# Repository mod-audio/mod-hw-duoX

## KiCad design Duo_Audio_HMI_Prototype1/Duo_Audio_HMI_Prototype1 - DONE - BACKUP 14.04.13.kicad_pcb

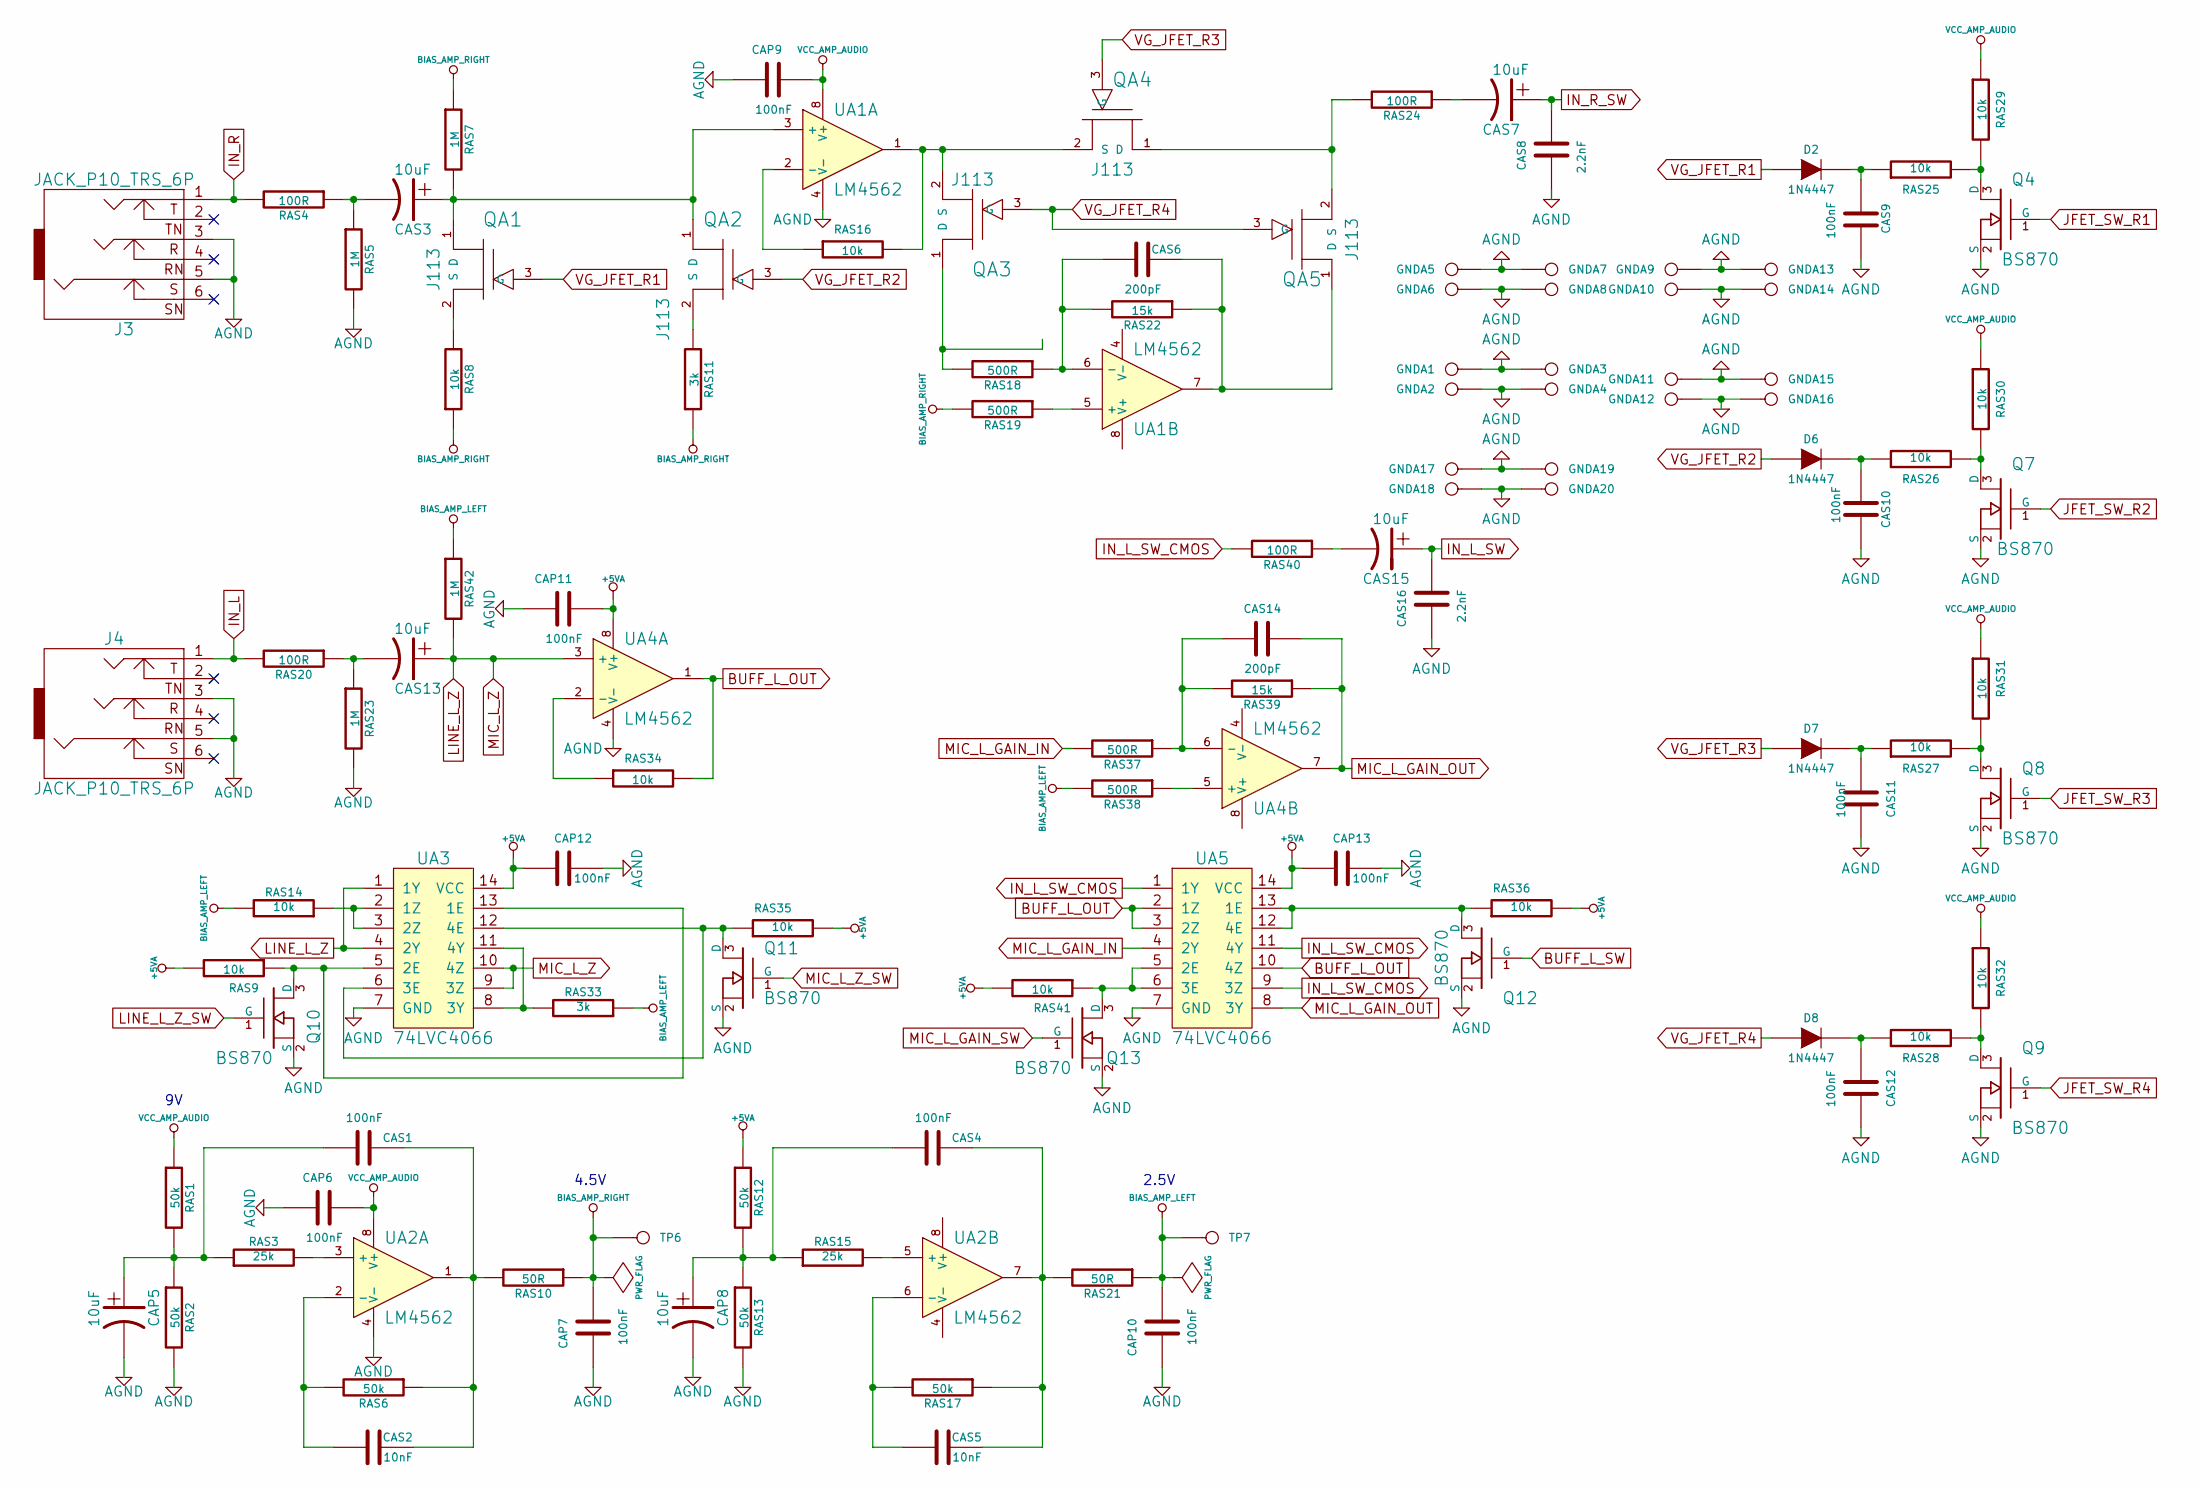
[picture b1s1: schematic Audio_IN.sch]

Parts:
CAP5, CAP8: 10uF; CAP_RAD_5MM
CAP6, CAP7, CAP9, CAP10, CAP11, CAP12, CAP13: 100nF; SM0603
CAS1, CAS4, CAS9, CAS10, CAS11, CAS12: 100nF; SM0603
CAS2, CAS5: 10nF; SM0603
CAS3, CAS7, CAS13, CAS15: 10uF; CAP_RAD_5MM
CAS6, CAS14: 200pF; SM0603
CAS8, CAS16: 2.2nF; SM0603
D2, D6, D7, D8: 1N4447; DO-35
GNDA1, GNDA2, GNDA3, GNDA4, GNDA5, GNDA6, GNDA7, GNDA8, GNDA9, GNDA10, GNDA11, GNDA12, GNDA13, GNDA14, GNDA15, GNDA16, GNDA17, GNDA18, GNDA19, GNDA20: CONN_1; PAD_GND
J3, J4: JACK_P10_TRS_6P; JACK-NMJ6HCD2_1
Q4, Q7, Q8, Q9, Q10, Q11, Q12, Q13: BS870; SOT23
QA1, QA2, QA3, QA4, QA5: J113; TO92_
RAS1, RAS2, RAS6, RAS12, RAS13, RAS17: 50k; RES_PTH_6MM
RAS3, RAS15: 25k; RES_PTH_6MM
RAS4, RAS20, RAS24, RAS40: 100R; RES_PTH_6MM
RAS5, RAS7, RAS23, RAS42: 1M; RES_PTH_6MM
RAS8, RAS14, RAS16, RAS25, RAS26, RAS27, RAS28, RAS29, RAS30, RAS31, RAS32, RAS34: 10k; RES_PTH_6MM
RAS9, RAS35, RAS36, RAS41: 10k; SM0603
RAS10, RAS21: 50R; RES_PTH_6MM
RAS11, RAS33: 3k; RES_PTH_6MM
RAS18, RAS19, RAS37, RAS38: 500R; RES_PTH_6MM
RAS22, RAS39: 15k; RES_PTH_6MM
TP6, TP7: CONN_1; SIL-1
UA1, UA2, UA4: LM4562; SO8E
UA3, UA5: 74LVC4066; SO14E

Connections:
+5VA: CAP11.2, CAP12.2, CAP13.2, RAS9.2, RAS12.1, RAS35.2, RAS36.2, RAS41.2, UA3.14 (VCC), UA4.8 (V+), UA5.14 (VCC); also elsewhere on the board
AGND: CAP5.2, CAP6.1, CAP7.1, CAP8.2, CAP9.1, CAP10.1, CAP11.1, CAP12.1, CAP13.1, CAS8.1, CAS9.2, CAS10.2, CAS11.2, CAS12.2, CAS16.1, GNDA1.1, GNDA2.1, GNDA3.1, GNDA4.1, GNDA5.1, GNDA6.1, GNDA7.1, GNDA8.1, GNDA9.1, GNDA10.1, GNDA11.1, GNDA12.1, GNDA13.1, GNDA14.1, GNDA15.1, GNDA16.1, GNDA17.1, GNDA18.1, GNDA19.1, GNDA20.1, J3.3, J3.5, J4.3, J4.5, Q4.2 (S), Q7.2 (S), Q8.2 (S), Q9.2 (S), Q10.2 (S), Q11.2 (S), Q12.2 (S), Q13.2 (S), RAS2.2, RAS5.2, RAS13.2, RAS23.2, UA1.4 (V-), UA2.4 (V-), UA3.7 (GND), UA4.4 (V-), UA5.7 (GND); also elsewhere on the board
BIAS_AMP_LEFT: CAP10.2, RAS14.2, RAS21.1, RAS33.1, RAS38.2, RAS42.1, TP7.1
BIAS_AMP_RIGHT: CAP7.2, RAS7.1, RAS8.1, RAS10.1, RAS11.1, RAS19.2, TP6.1
BUFF_L_OUT: RAS34.2, UA4.1, UA5.2 (1Z), UA5.3 (2Z), UA5.10 (4Z)
BUFF_L_SW: Q12.1 (G); also elsewhere on the board
IN_L: J4.1, RAS20.2; also elsewhere on the board
IN_L_SW: CAS15.1, CAS16.2; also elsewhere on the board
IN_L_SW_CMOS: RAS40.2, UA5.1 (1Y), UA5.9 (3Z), UA5.11 (4Y)
IN_R: J3.1, RAS4.2; also elsewhere on the board
IN_R_SW: CAS7.1, CAS8.2; also elsewhere on the board
JFET_SW_R1: Q4.1 (G); also elsewhere on the board
JFET_SW_R2: Q7.1 (G); also elsewhere on the board
JFET_SW_R3: Q8.1 (G); also elsewhere on the board
JFET_SW_R4: Q9.1 (G); also elsewhere on the board
LINE_L_Z: CAS13.1, RAS42.2, UA3.1 (1Y), UA3.4 (2Y), UA3.9 (3Z), UA3.10 (4Z), UA4.3 (+)
LINE_L_Z_SW: Q10.1 (G); also elsewhere on the board
MIC_L_GAIN_IN: RAS37.2, UA5.4 (2Y)
MIC_L_GAIN_OUT: CAS14.2, RAS39.1, UA4.7, UA5.8 (3Y)
MIC_L_GAIN_SW: Q13.1 (G); also elsewhere on the board
MIC_L_Z_SW: Q11.1 (G); also elsewhere on the board
unnamed: QA4.1 (D), QA5.2 (S), RAS24.2
unnamed: QA2.2 (S), RAS11.2
unnamed: QA1.2 (S), RAS8.2
unnamed: CAS13.2, RAS20.1, RAS23.1
unnamed: QA3.1 (D), RAS18.2
unnamed: Q9.3 (D), RAS28.2, RAS32.2
unnamed: CAS15.2, RAS40.1
unnamed: RAS14.1, UA3.2 (1Z), UA3.3 (2Z)
unnamed: RAS34.1, UA4.2 (-)
unnamed: RAS38.1, UA4.5 (+)
unnamed: CAS14.1, RAS37.1, RAS39.2, UA4.6 (-)
unnamed: CAS5.1, RAS17.2, UA2.6 (-)
unnamed: CAS3.2, RAS4.1, RAS5.1
unnamed: CAS3.1, QA1.1 (D), QA2.1 (D), RAS7.2, UA1.3 (+)
unnamed: RAS16.1, UA1.2 (-)
unnamed: CAP8.1, CAS4.1, RAS12.2, RAS13.1, RAS15.1
unnamed: RAS15.2, UA2.5 (+)
unnamed: CAS4.2, CAS5.2, RAS17.1, RAS21.2, UA2.7
unnamed: CAS7.2, RAS24.1
unnamed: Q4.3 (D), RAS25.2, RAS29.2
unnamed: Q8.3 (D), RAS27.2, RAS31.2
unnamed: CAS6.2, QA5.1 (D), RAS22.1, UA1.7
unnamed: QA3.2 (S), QA4.2 (S), RAS16.2, UA1.1
unnamed: RAS19.1, UA1.5 (+)
unnamed: CAS6.1, RAS18.1, RAS22.2, UA1.6 (-)
unnamed: Q7.3 (D), RAS26.2, RAS30.2
unnamed: CAS12.1, D8.2 (K), RAS28.1
unnamed: CAS11.1, D7.2 (K), RAS27.1
unnamed: CAS10.1, D6.2 (K), RAS26.1
unnamed: CAS9.1, D2.2 (K), RAS25.1
unnamed: Q13.3 (D), RAS41.1, UA5.5 (2E), UA5.6 (3E)
unnamed: RAS33.2, UA3.8 (3Y), UA3.11 (4Y)
unnamed: Q11.3 (D), RAS35.1, UA3.6 (3E), UA3.12 (4E)
unnamed: Q10.3 (D), RAS9.1, UA3.5 (2E), UA3.13 (1E)
unnamed: Q12.3 (D), RAS36.1, UA5.12 (4E), UA5.13 (1E)
unnamed: CAP5.1, CAS1.1, RAS1.2, RAS2.1, RAS3.1
unnamed: CAS2.1, RAS6.2, UA2.2 (-)
unnamed: RAS3.2, UA2.3 (+)
unnamed: CAS1.2, CAS2.2, RAS6.1, RAS10.2, UA2.1
VCC_AMP_AUDIO: CAP6.2, CAP9.2, RAS1.1, RAS29.1, RAS30.1, RAS31.1, RAS32.1, UA1.8 (V+), UA2.8 (V+); also elsewhere on the board
VG_JFET_R1: D2.1 (A), QA1.3 (G)
VG_JFET_R2: D6.1 (A), QA2.3 (G)
VG_JFET_R3: D7.1 (A), QA4.3 (G)
VG_JFET_R4: D8.1 (A), QA3.3 (G), QA5.3 (G)

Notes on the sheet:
4.5V
2.5V

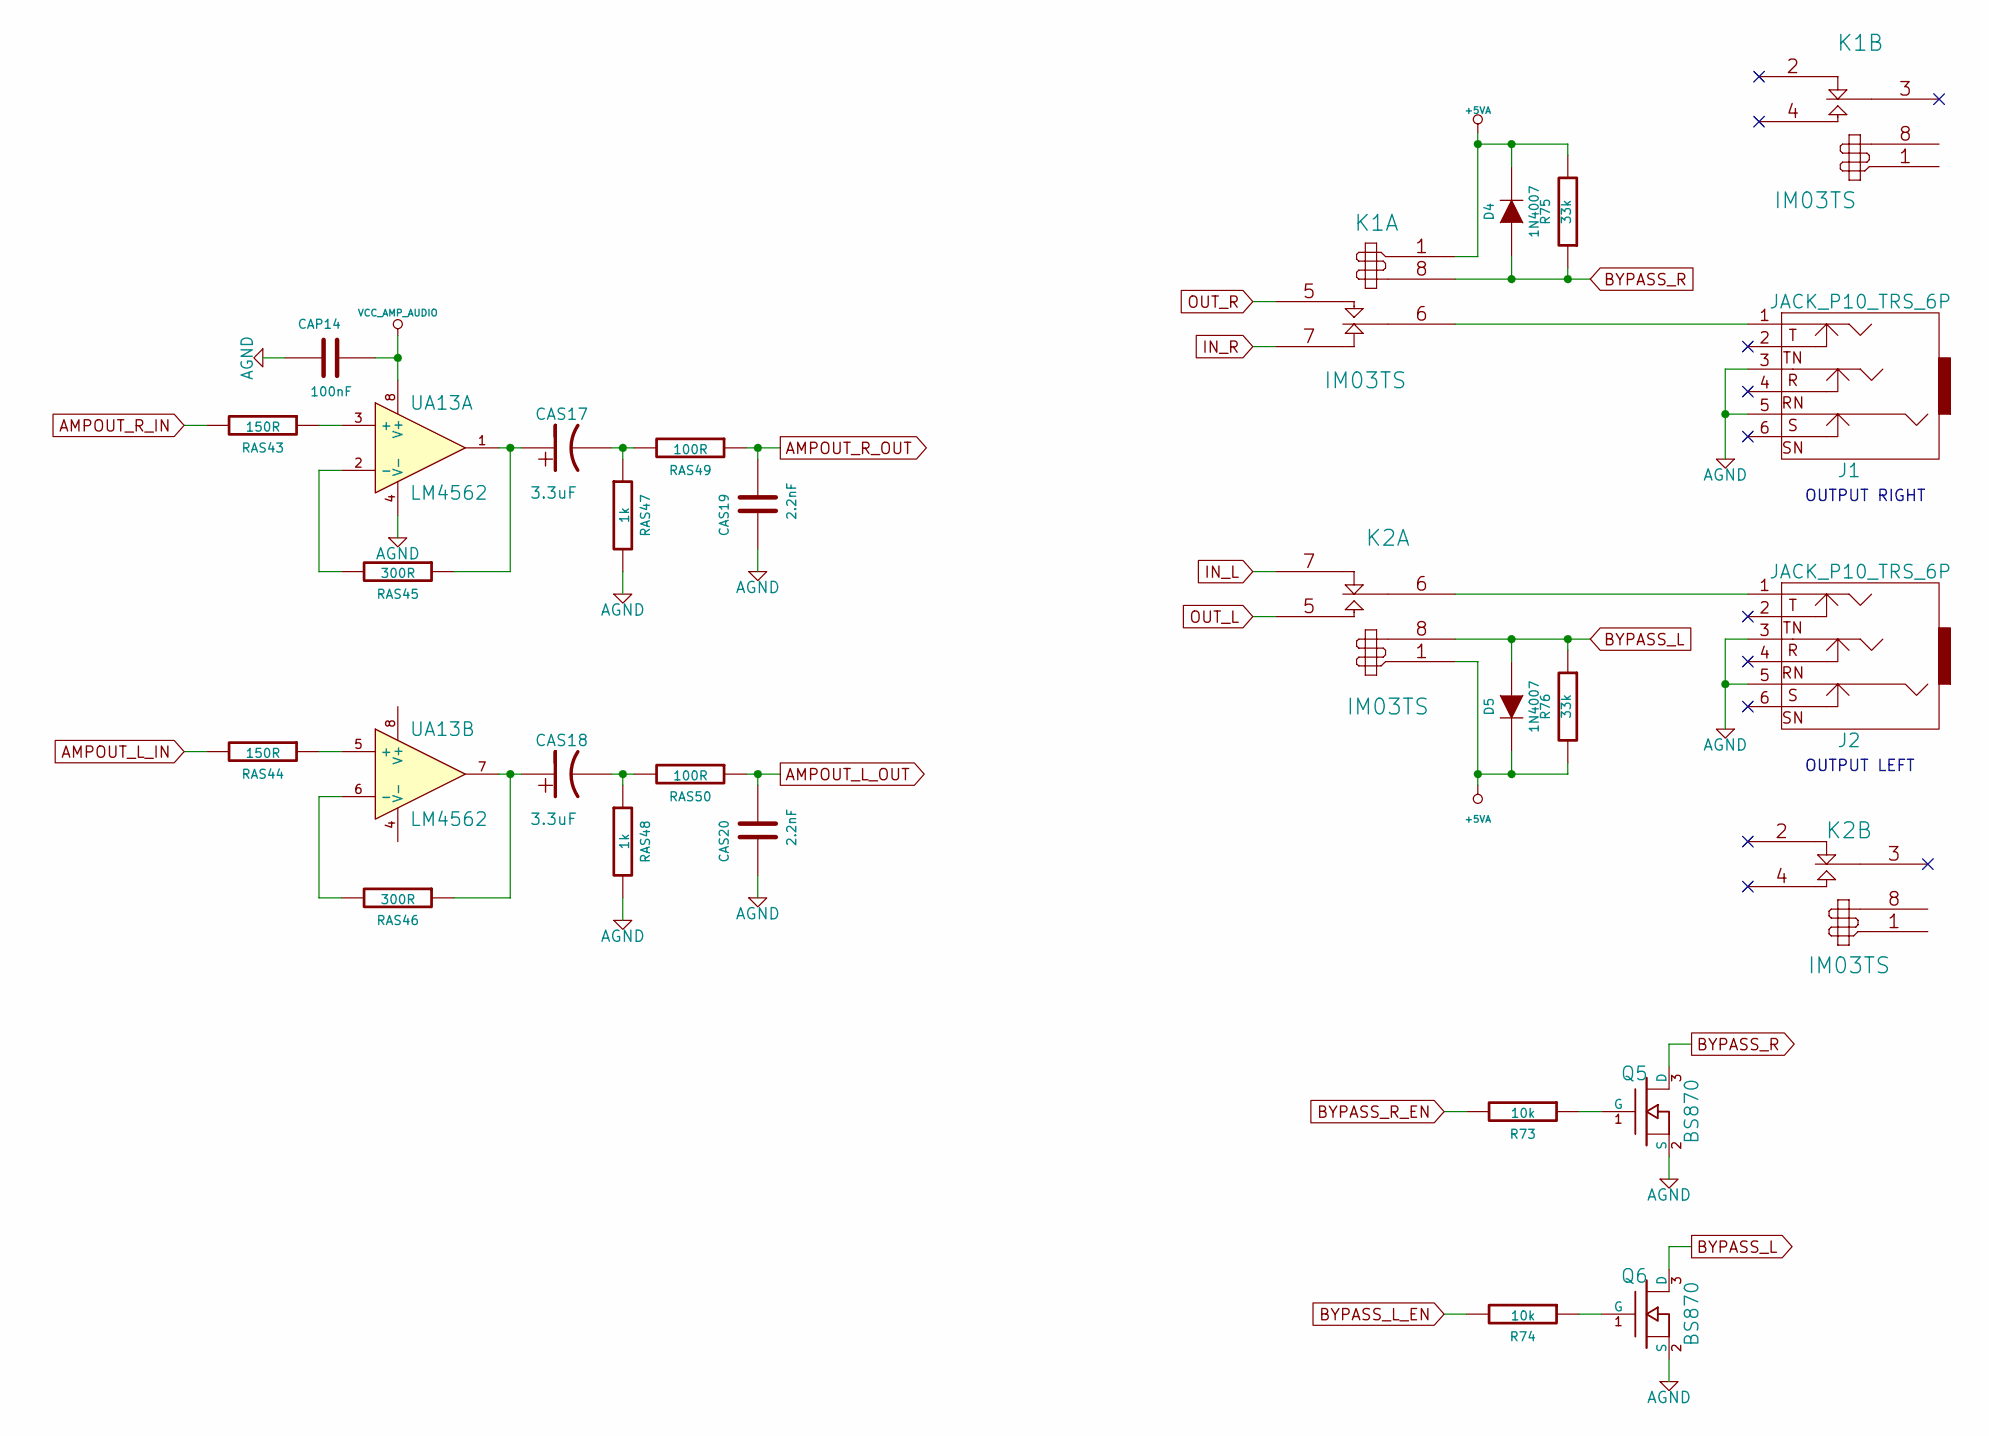
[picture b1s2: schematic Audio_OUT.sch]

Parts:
CAP14: 100nF; SM0603
CAS17, CAS18: 3.3uF; CAP_RAD_5MM
CAS19, CAS20: 2.2nF; SM0603
D4, D5: 1N4007; DO-214AC(SMA)
J1, J2: JACK_P10_TRS_6P; JACK-NMJ6HCD2_1
K1, K2: IM03TS
Q5, Q6: BS870; SOT23
R73, R74: 10k; SM0603
R75, R76: 33k; SM0603
RAS43, RAS44: 150R; RES_PTH_6MM
RAS45, RAS46: 300R; RES_PTH_6MM
RAS47, RAS48: 1k; RES_PTH_6MM
RAS49, RAS50: 100R; RES_PTH_6MM
UA13: LM4562; SO8E

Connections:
+5VA: D4.2 (K), D5.2 (K), K1.1, K2.1, R75.2, R76.2; also elsewhere on the board
AGND: CAP14.1, CAS19.1, CAS20.1, J1.3, J1.5, J2.3, J2.5, Q5.2 (S), Q6.2 (S), RAS47.2, RAS48.2, UA13.4 (V-); also elsewhere on the board
AMPOUT_L_IN: RAS44.2; also elsewhere on the board
AMPOUT_L_OUT: CAS20.2, RAS50.1; also elsewhere on the board
AMPOUT_R_IN: RAS43.2; also elsewhere on the board
AMPOUT_R_OUT: CAS19.2, RAS49.1; also elsewhere on the board
BYPASS_L: D5.1 (A), K2.8, Q6.3 (D), R76.1
BYPASS_L_EN: R74.2; also elsewhere on the board
BYPASS_R: D4.1 (A), K1.8, Q5.3 (D), R75.1
BYPASS_R_EN: R73.2; also elsewhere on the board
IN_L: K2.7 (R); also elsewhere on the board
IN_R: K1.7 (R); also elsewhere on the board
unnamed: RAS44.1, UA13.5 (+)
unnamed: CAS18.1, RAS46.1, UA13.7
unnamed: RAS46.2, UA13.6 (-)
unnamed: RAS43.1, UA13.3 (+)
unnamed: CAS17.2, RAS47.1, RAS49.2
unnamed: J1.1, K1.6 (C)
unnamed: J2.1, K2.6 (C)
unnamed: CAS18.2, RAS48.1, RAS50.2
unnamed: Q5.1 (G), R73.1
unnamed: Q6.1 (G), R74.1
unnamed: RAS45.2, UA13.2 (-)
unnamed: CAS17.1, RAS45.1, UA13.1
OUT_L: K2.5 (T); also elsewhere on the board
OUT_R: K1.5 (T); also elsewhere on the board
VCC_AMP_AUDIO: CAP14.2, UA13.8 (V+); also elsewhere on the board

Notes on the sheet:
OUTPUT RIGHT
OUTPUT LEFT

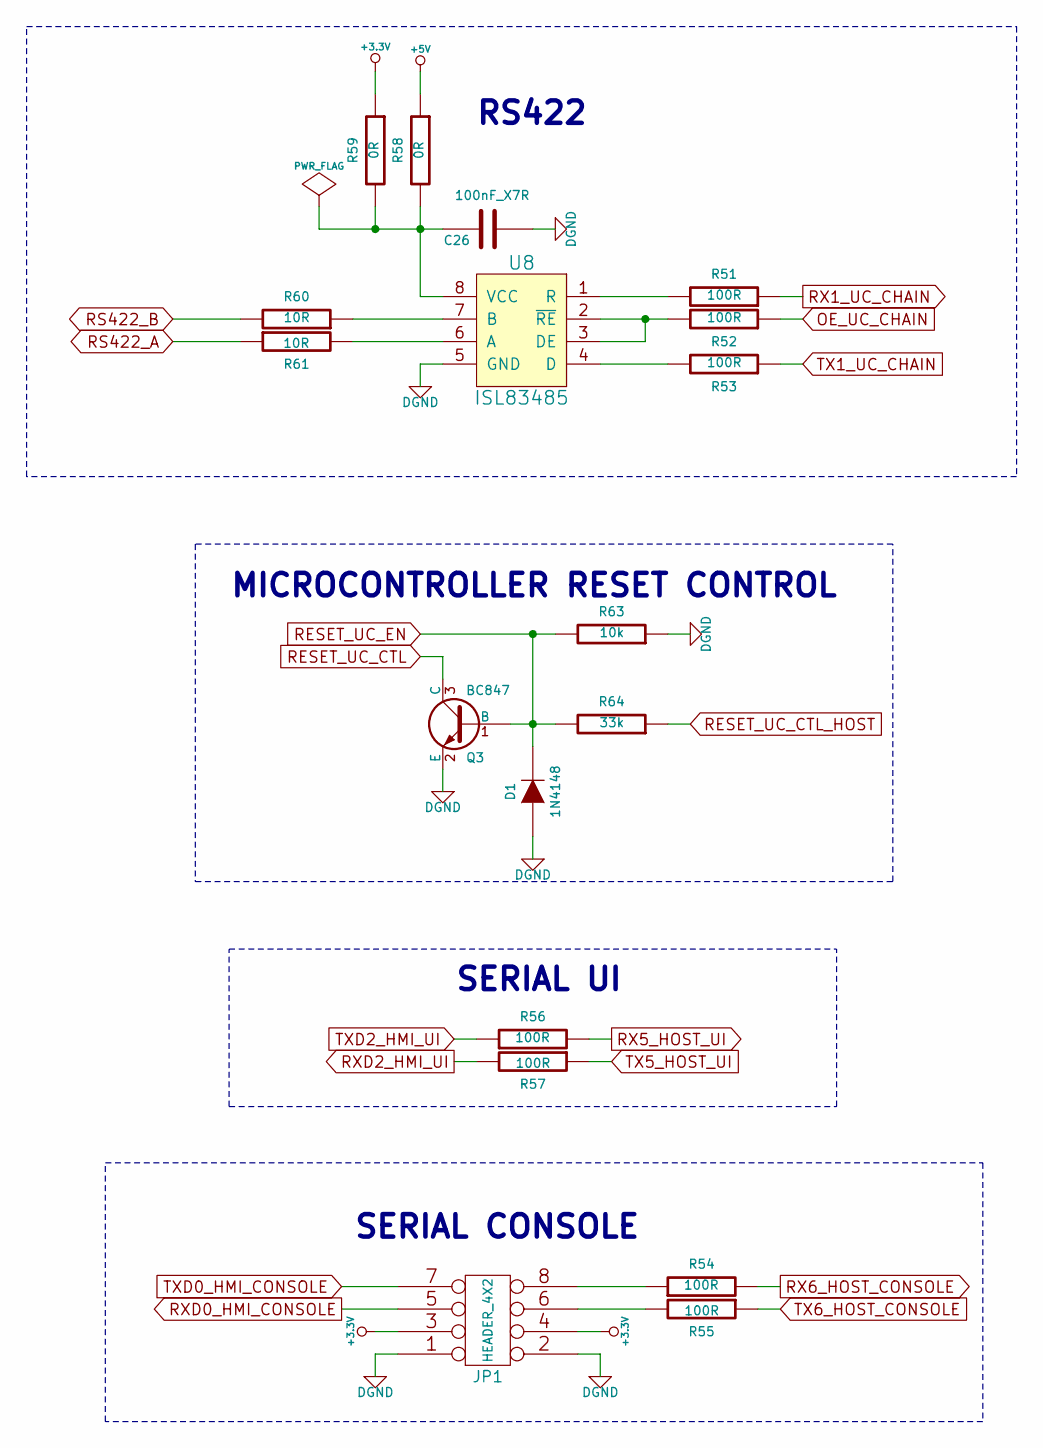
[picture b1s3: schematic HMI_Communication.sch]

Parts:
C26: 100nF_X7R; SM0603
D1: 1N4148; SOD323
JP1: HEADER_4X2; PIN_ARRAY_4X2
Q3: BC847; SOT23
R51, R52, R53, R54, R55, R56, R57: 100R; SM0603
R58, R59: 0R; SM0805
R60, R61: 10R; SM0805
R63: 10k; SM0603
R64: 33k; SM0603
U8: ISL83485; SO8E

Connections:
+3.3V: JP1.3, JP1.4, R59.1; also elsewhere on the board
+5V: R58.1; also elsewhere on the board
AGND: C26.1, D1.1 (A), JP1.1, JP1.2, Q3.2 (E), R63.1, U8.5 (GND); also elsewhere on the board
unnamed: R53.2, U8.4 (D)
unnamed: JP1.8, R54.1
unnamed: C26.2, R58.2, R59.2, U8.8 (VCC)
unnamed: R51.2, U8.1 (R)
unnamed: R61.2, U8.6 (A)
unnamed: R60.1, U8.7 (B)
unnamed: R52.2, U8.2 (~RE), U8.3 (DE)
unnamed: JP1.6, R55.2
OE_UC_CHAIN: R52.1; also elsewhere on the board
RESET_UC_CTL: Q3.3 (C); also elsewhere on the board
RESET_UC_CTL_HOST: R64.1; also elsewhere on the board
RESET_UC_EN: D1.2 (K), Q3.1 (B), R63.2, R64.2; also elsewhere on the board
RS422_A: R61.1; also elsewhere on the board
RS422_B: R60.2; also elsewhere on the board
RX1_UC_CHAIN: R51.1; also elsewhere on the board
RX5_HOST_UI: R56.2; also elsewhere on the board
RX6_HOST_CONSOLE: R54.2; also elsewhere on the board
RXD0_HMI_CONSOLE: JP1.5; also elsewhere on the board
RXD2_HMI_UI: R57.2; also elsewhere on the board
TX1_UC_CHAIN: R53.1; also elsewhere on the board
TX5_HOST_UI: R57.1; also elsewhere on the board
TX6_HOST_CONSOLE: R55.1; also elsewhere on the board
TXD0_HMI_CONSOLE: JP1.7; also elsewhere on the board
TXD2_HMI_UI: R56.1; also elsewhere on the board

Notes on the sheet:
RS422
SERIAL UI
SERIAL CONSOLE
MICROCONTROLLER RESET CONTROL

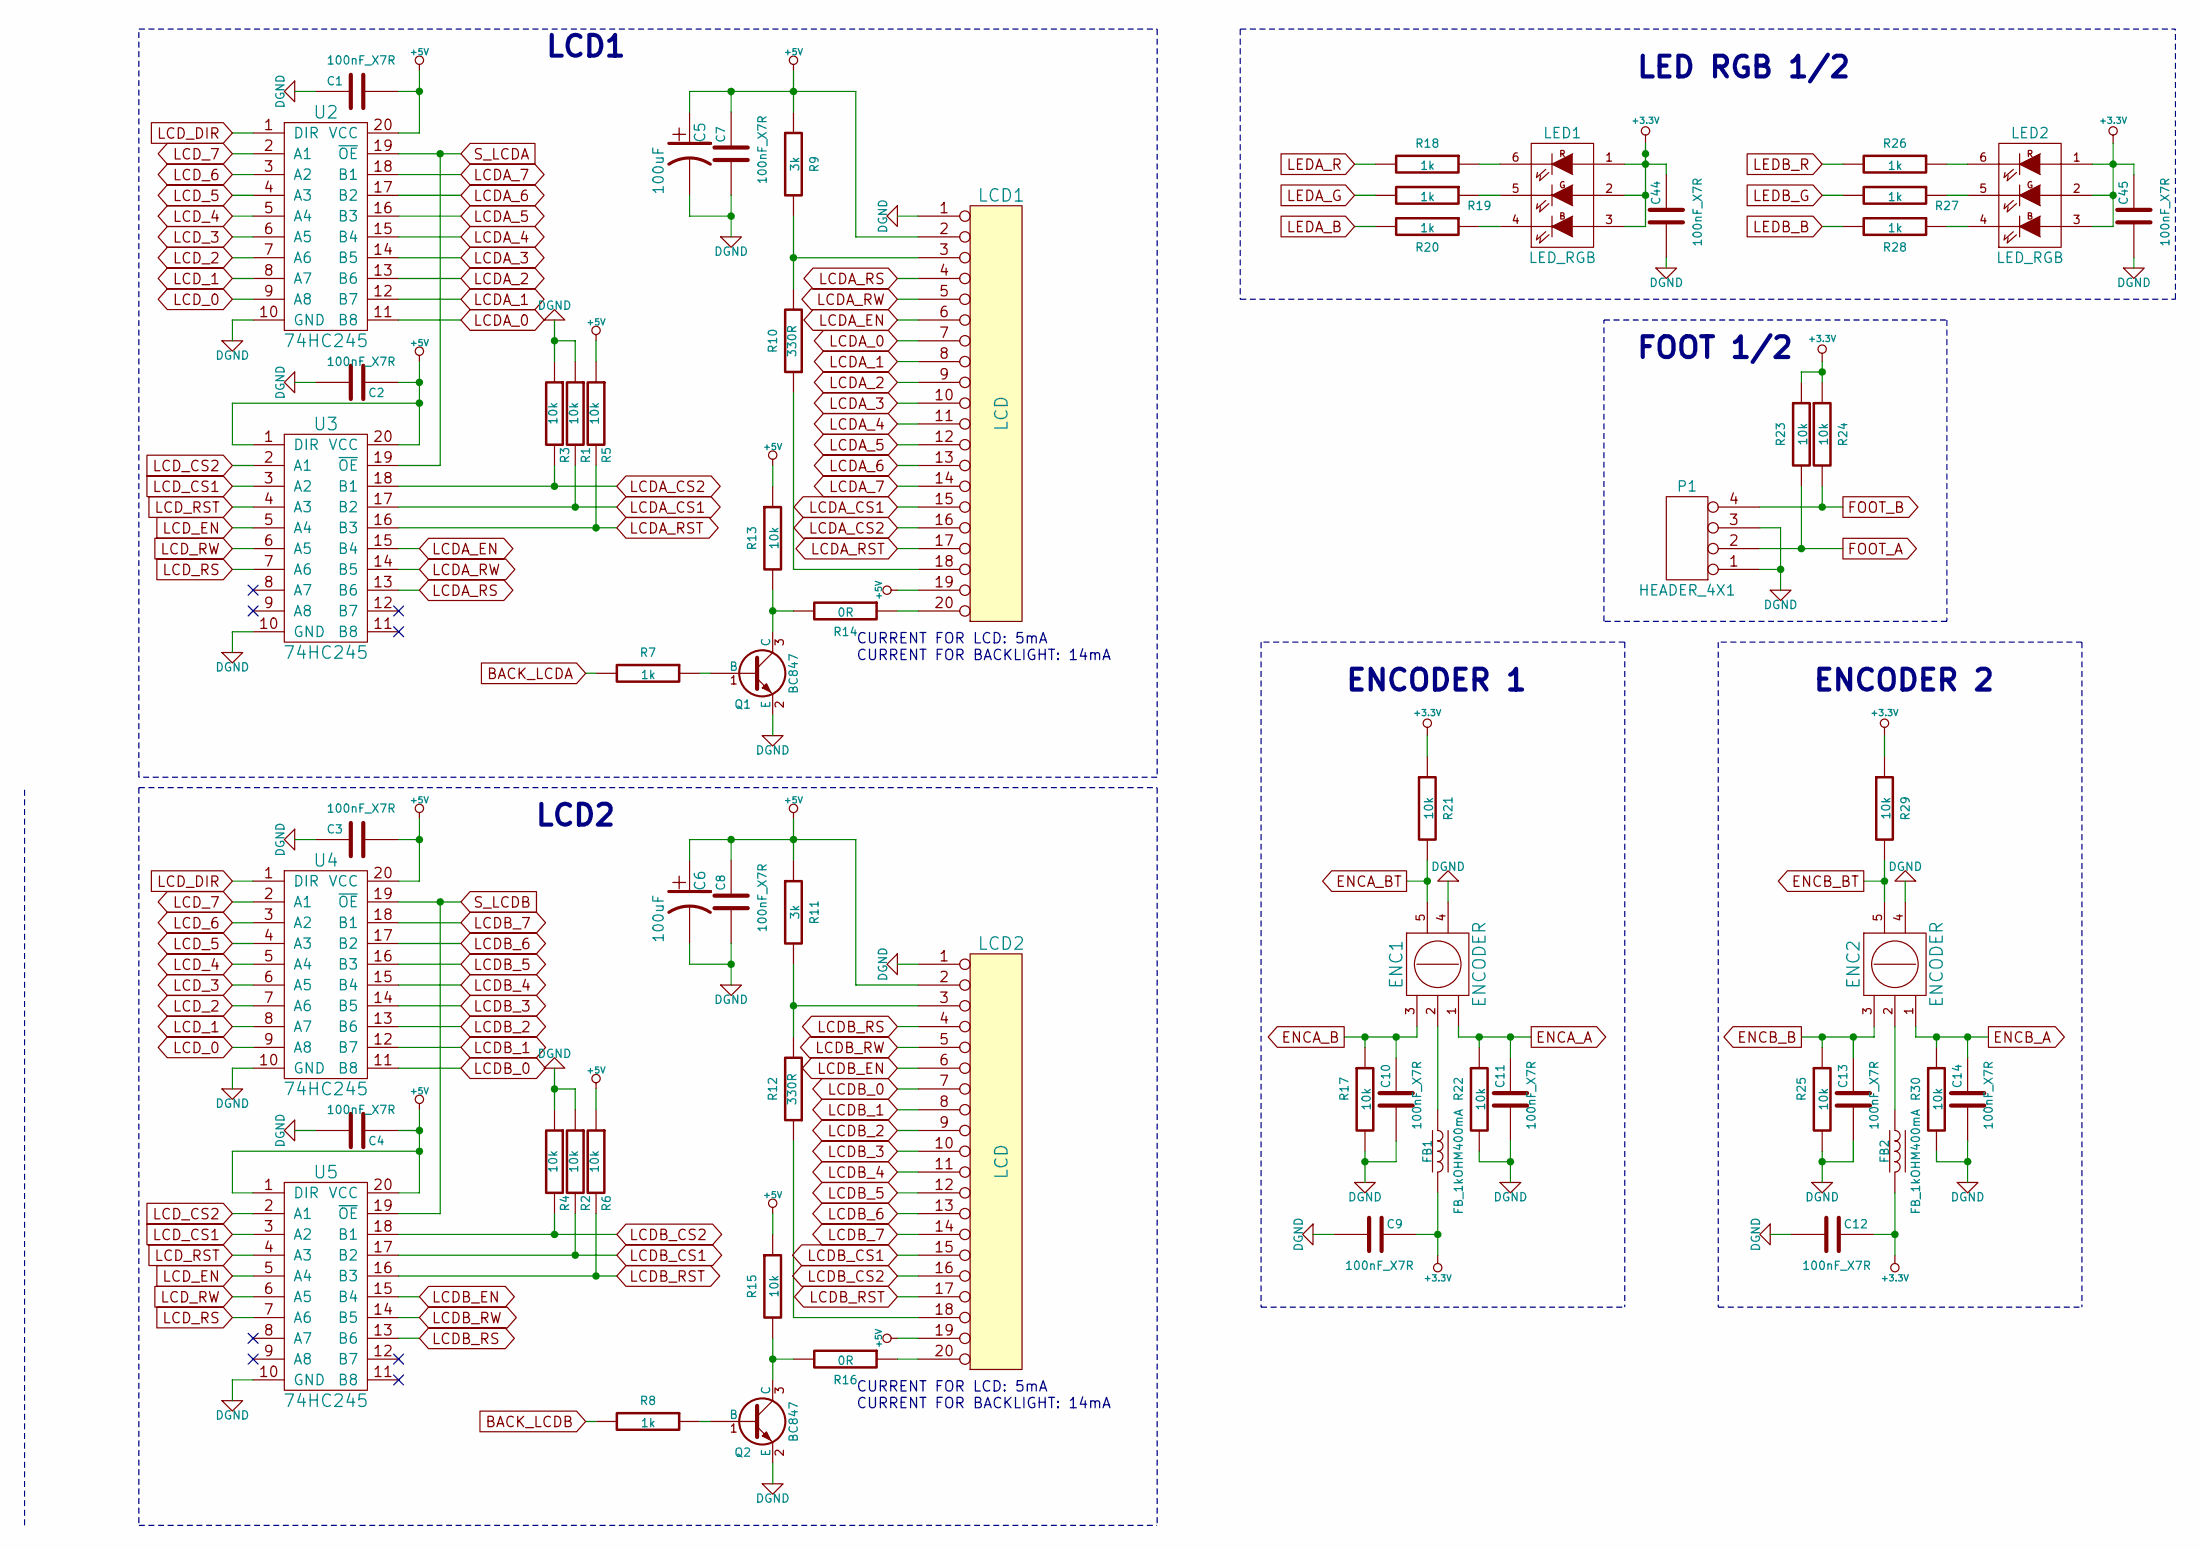
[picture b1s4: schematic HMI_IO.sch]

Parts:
C1, C2, C3, C4, C7, C8, C9, C10, C11, C12, C13, C14, C44, C45: 100nF_X7R; SM0603
C5, C6: 100uF; CAP_RAD_5MM
ENC1, ENC2: ENCODER; ENCODER_PEC11_4KS1
FB1, FB2: FB_1kOHM400mA; SM0805
LCD1, LCD2: LCD; LCD-AGM-12864E1-201_1
LED1, LED2: LED_RGB; LED_CLRTB_GFSF_1
P1: HEADER_4X1; PIN_ARRAY_4x1
Q1, Q2: BC847; SOT23
R1, R2, R3, R4, R5, R6, R13, R15, R17, R21, R22, R23, R24, R25, R29, R30: 10k; SM0603
R7, R8, R18, R19, R20, R26, R27, R28: 1k; SM0603
R9, R11: 3k; SM0603
R10, R12: 330R; SM0603
R14, R16: 0R; SM0805
U2, U3, U4, U5: 74HC245; TSSOP20

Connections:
+3.3V: C9.1, C12.1, C44.1, C45.1, FB1.1, FB2.1, LED1.1 (AR), LED1.2 (AG), LED1.3 (AB), LED2.1 (AR), LED2.2 (AG), LED2.3 (AB), R21.1, R23.1, R24.1, R29.1; also elsewhere on the board
+5V: C1.1, C2.1, C3.1, C4.1, C5.1, C6.1, C7.1, C8.1, LCD1.2, LCD1.19, LCD2.2, LCD2.19, R5.1, R6.1, R9.1, R11.1, R13.1, R15.1, U2.20 (VCC), U3.1 (DIR), U3.20 (VCC), U4.20 (VCC), U5.1 (DIR), U5.20 (VCC); also elsewhere on the board
AGND: C1.2, C2.2, C3.2, C4.2, C5.2, C6.2, C7.2, C8.2, C9.2, C10.2, C11.2, C12.2, C13.2, C14.2, C44.2, C45.2, ENC1.4, ENC2.4, LCD1.1, LCD2.1, P1.1, P1.3, Q1.2 (E), Q2.2 (E), R1.1, R2.1, R3.1, R4.1, R17.2, R22.2, R25.2, R30.2, U2.10 (GND), U3.10 (GND), U4.10 (GND), U5.10 (GND); also elsewhere on the board
BACK_LCDA: R7.2; also elsewhere on the board
BACK_LCDB: R8.2; also elsewhere on the board
ENCA_A: C11.1, ENC1.1, R22.1; also elsewhere on the board
ENCA_B: C10.1, ENC1.3, R17.1; also elsewhere on the board
ENCA_BT: ENC1.5, R21.2; also elsewhere on the board
ENCB_A: C14.1, ENC2.1, R30.1; also elsewhere on the board
ENCB_B: C13.1, ENC2.3, R25.1; also elsewhere on the board
ENCB_BT: ENC2.5, R29.2; also elsewhere on the board
FOOT_A: P1.2, R23.2; also elsewhere on the board
FOOT_B: P1.4, R24.2; also elsewhere on the board
LCDA_0: LCD1.7, U2.11 (B8)
LCDA_1: LCD1.8, U2.12 (B7)
LCDA_2: LCD1.9, U2.13 (B6)
LCDA_3: LCD1.10, U2.14 (B5)
LCDA_4: LCD1.11, U2.15 (B4)
LCDA_5: LCD1.12, U2.16 (B3)
LCDA_6: LCD1.13, U2.17 (B2)
LCDA_7: LCD1.14, U2.18 (B1)
LCDA_CS1: LCD1.15, R1.2, U3.17 (B2)
LCDA_CS2: LCD1.16, R3.2, U3.18 (B1)
LCDA_EN: LCD1.6, U3.15 (B4)
LCDA_RS: LCD1.4, U3.13 (B6)
LCDA_RST: LCD1.17, R5.2, U3.16 (B3)
LCDA_RW: LCD1.5, U3.14 (B5)
LCDB_0: LCD2.7, U4.11 (B8)
LCDB_1: LCD2.8, U4.12 (B7)
LCDB_2: LCD2.9, U4.13 (B6)
LCDB_3: LCD2.10, U4.14 (B5)
LCDB_4: LCD2.11, U4.15 (B4)
LCDB_5: LCD2.12, U4.16 (B3)
LCDB_6: LCD2.13, U4.17 (B2)
LCDB_7: LCD2.14, U4.18 (B1)
LCDB_CS1: LCD2.15, R2.2, U5.17 (B2)
LCDB_CS2: LCD2.16, R4.2, U5.18 (B1)
LCDB_EN: LCD2.6, U5.15 (B4)
LCDB_RS: LCD2.4, U5.13 (B6)
LCDB_RST: LCD2.17, R6.2, U5.16 (B3)
LCDB_RW: LCD2.5, U5.14 (B5)
LCD_0: U2.9 (A8), U4.9 (A8); also elsewhere on the board
LCD_1: U2.8 (A7), U4.8 (A7); also elsewhere on the board
LCD_2: U2.7 (A6), U4.7 (A6); also elsewhere on the board
LCD_3: U2.6 (A5), U4.6 (A5); also elsewhere on the board
LCD_4: U2.5 (A4), U4.5 (A4); also elsewhere on the board
LCD_5: U2.4 (A3), U4.4 (A3); also elsewhere on the board
LCD_6: U2.3 (A2), U4.3 (A2); also elsewhere on the board
LCD_7: U2.2 (A1), U4.2 (A1); also elsewhere on the board
LCD_CS1: U3.3 (A2), U5.3 (A2); also elsewhere on the board
LCD_CS2: U3.2 (A1), U5.2 (A1); also elsewhere on the board
LCD_DIR: U2.1 (DIR), U4.1 (DIR); also elsewhere on the board
LCD_EN: U3.5 (A4), U5.5 (A4); also elsewhere on the board
LCD_RS: U3.7 (A6), U5.7 (A6); also elsewhere on the board
LCD_RST: U3.4 (A3), U5.4 (A3); also elsewhere on the board
LCD_RW: U3.6 (A5), U5.6 (A5); also elsewhere on the board
LEDA_B: R20.2; also elsewhere on the board
LEDA_G: R19.2; also elsewhere on the board
LEDA_R: R18.2; also elsewhere on the board
LEDB_B: R28.2; also elsewhere on the board
LEDB_G: R27.2; also elsewhere on the board
LEDB_R: R26.2; also elsewhere on the board
unnamed: LCD1.18, R10.1
unnamed: Q1.1 (B), R7.1
unnamed: ENC2.2, FB2.2
unnamed: ENC1.2, FB1.2
unnamed: Q2.1 (B), R8.1
unnamed: LCD1.3, R9.2, R10.2
unnamed: LCD2.3, R11.2, R12.2
unnamed: LCD1.20, R14.1
unnamed: Q1.3 (C), R13.2, R14.2
unnamed: LCD2.18, R12.1
unnamed: LCD2.20, R16.1
unnamed: Q2.3 (C), R15.2, R16.2
unnamed: LED1.6 (KR), R18.1
unnamed: LED1.5 (KG), R19.1
unnamed: LED1.4 (KB), R20.1
unnamed: LED2.4 (KB), R28.1
unnamed: LED2.6 (KR), R26.1
unnamed: LED2.5 (KG), R27.1
S_LCDA: U2.19 (~OE), U3.19 (~OE); also elsewhere on the board
S_LCDB: U4.19 (~OE), U5.19 (~OE); also elsewhere on the board

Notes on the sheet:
CURRENT FOR LCD: 5mA CURRENT FOR BACKLIGHT: 14mA
LCD1
LCD2
LED RGB 1/2
ENCODER 1
ENCODER 2
FOOT 1/2
